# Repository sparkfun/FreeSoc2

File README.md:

SparkFun FreeSoc2
========================================

[*SparkFun FreeSoC2 (DEV-13714)*](https://www.sparkfun.com/products/13714)

The [FreeSoc2 is SparkFun's PSoC5LP development board](https://www.sparkfun.com/products/13714). It features a full onboard debugger, support for 5V and 3.3V IO voltages, and a CY8C5888AXI-LP096 processor with 256kB of flash, 64kB of SRAM and 2kB of EEPROM. The onboard oscillator can drive the processor at up to 80MHz, and the Cortex-M3 core provides superior performance.

The real power of the PSoC5LP isn't in the processor, however. Wrapped around the processor is a rich analog and digital programmable fabric which can be configured to provide many functions which would otherwise need to be realized in code (lowering system performance) or external circuitry (adding cost and board size). In addition, the highly flexible fabric means that most any function can be routed to most any pin, which makes this a wonderful tool for development and allows board layout errors to be solved, at least temporarily, pretty easily.

Repository Contents
-------------------

* **/Hardware** - Eagle design files (.brd, .sch)
* **/Production** - Production panel files (.brd)

Documentation
--------------
* **[Arduino Board Support](https://github.com/sparkfun/PSoC_Arduino_Support)** - Support board files for adding the FreeSoC2 to the Arduino IDE.
* **[Hookup Guide](https://learn.sparkfun.com/tutorials/freesoc2-hookup-guide-v14)** - Basic hookup guide for the FreeSoC2.

Product Versions
----------------
* [DEV-13714](https://www.sparkfun.com/products/13714) - V14
* _[DEV-13229 (RETIRED)](https://www.sparkfun.com/products/13229)- Initial Release_

Version History
---------------
* [v14](https://github.com/sparkfun/FreeSoc2/releases/tag/v14) -  V14 update
* [v01](https://github.com/sparkfun/FreeSoc2/releases/tag/v01) - Initial Release

License Information
-------------------
This product is _**open source**_! 

The **hardware** is released under [Creative Commons ShareAlike 4.0 International](https://creativecommons.org/licenses/by-sa/4.0/).

The **code** is beerware; if you see me (or any other SparkFun employee) at the local, and you've found our code helpful, please buy us a round!

Please use, reuse, and modify these files as you see fit. Please maintain attribution to SparkFun Electronics and release anything derivative under the same license.

Distributed as-is; no warranty is given.

- Your friends at SparkFun.

Collaborators
-------------

Thanks to Jon Moeller, for creating the first FreeSoC board and providing terrific feedback during the development of the FreeSoC2.
Thanks to Cypress Semiconductor, for providing feedback and working with us closely to ensure that the FreeSoC2 was the right product for the time.

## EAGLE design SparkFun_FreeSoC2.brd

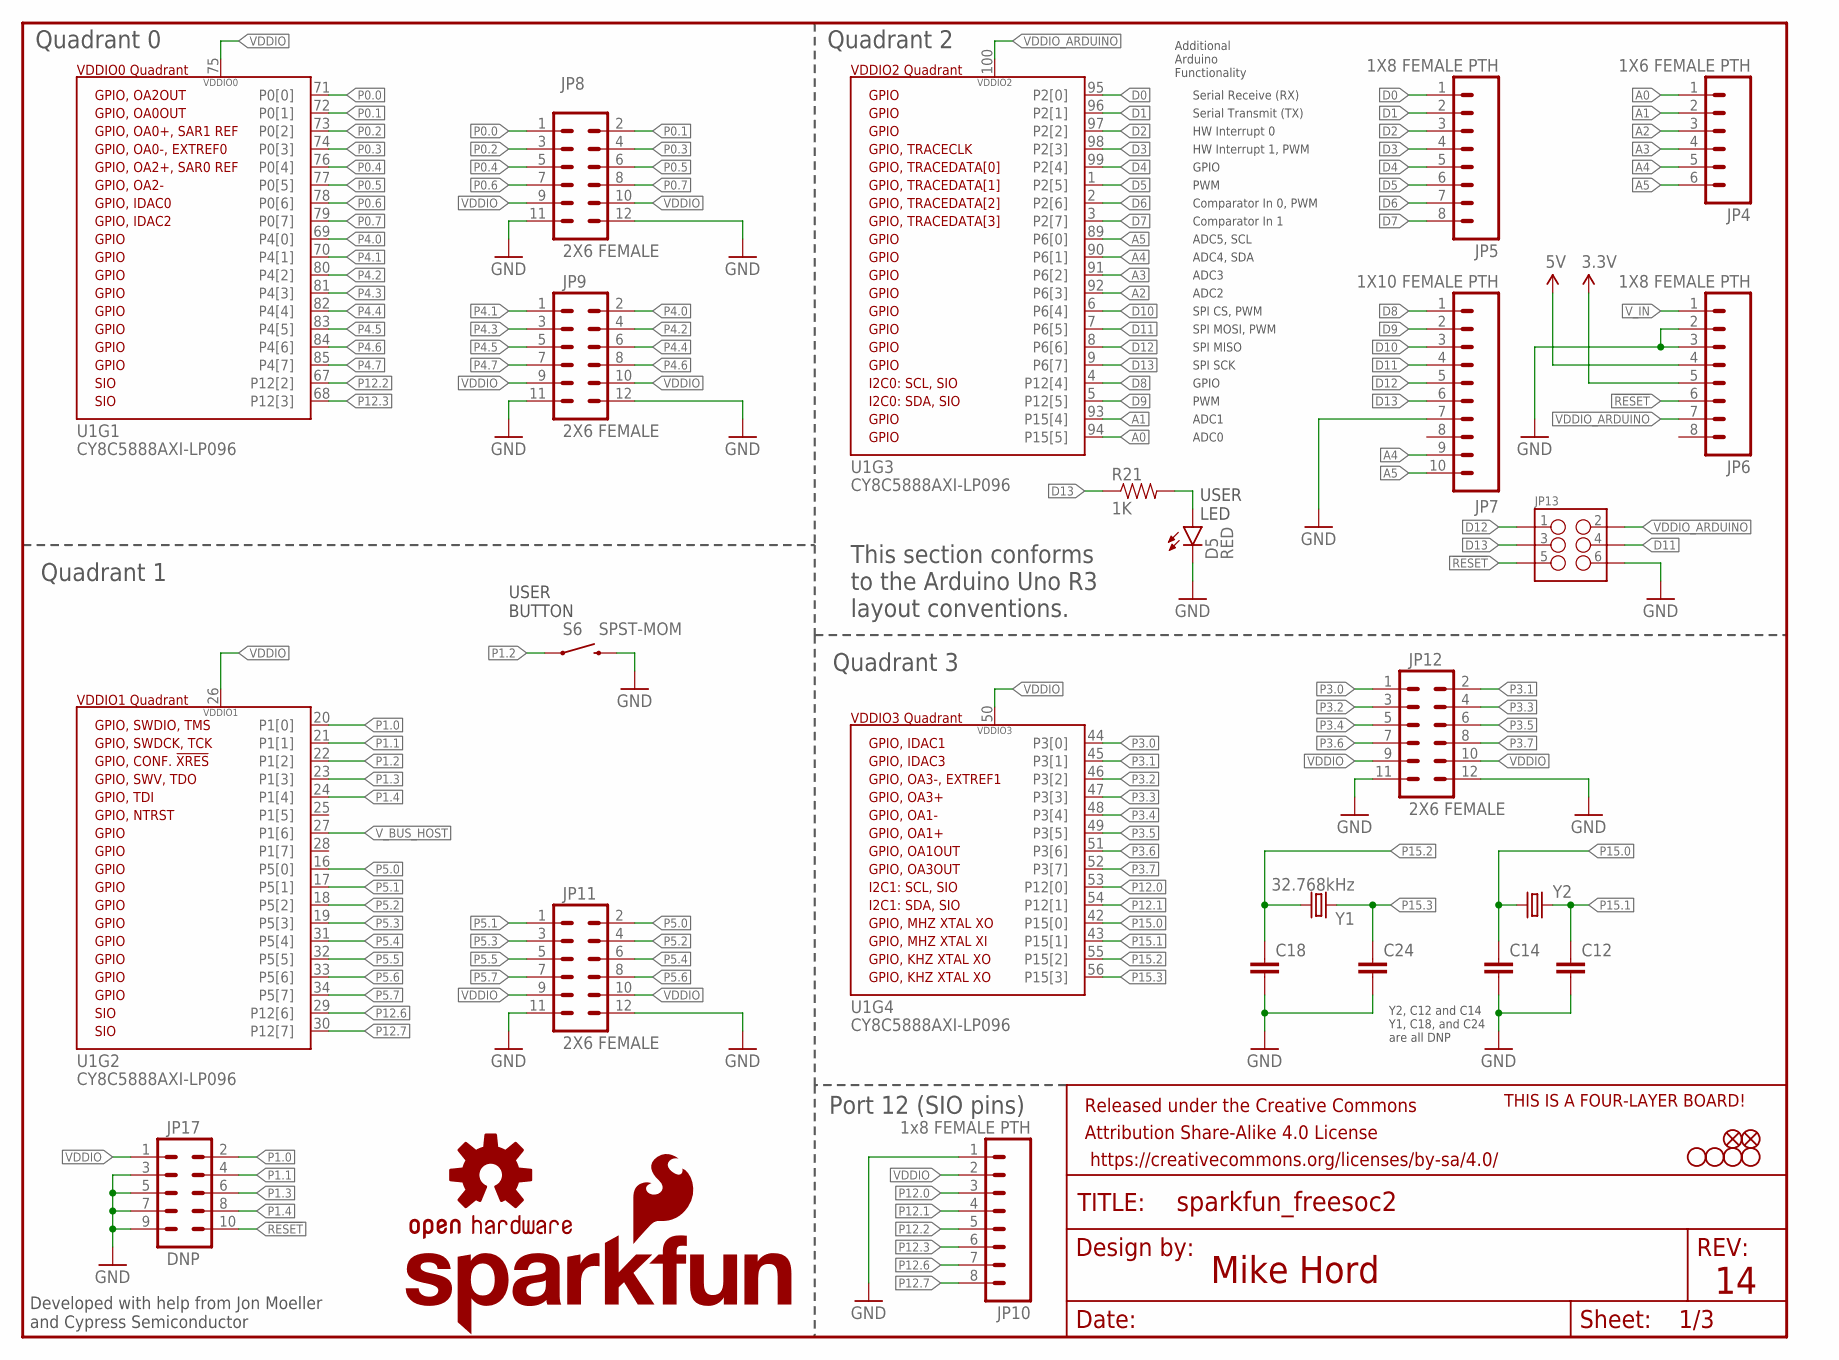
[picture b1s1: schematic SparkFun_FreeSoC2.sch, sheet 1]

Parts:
C12, C14, C18, C24: CAPPTH; CAP-PTH-SMALL
D5: RED; LED-0603
FID1, FID2: FIDUCIAL1X2; FIDUCIAL-1X2
FRAME3: FRAME-LETTERNO_PACKAGE; DUMMY
JP4: 1X6 FEMALE PTH; 1X06-SIP_LOCK
JP5, JP6: 1X8 FEMALE PTH; 1X08_LOCK
JP7: 1X10 FEMALE PTH; 1X10_LOCK
JP8, JP9, JP11, JP12: 2X6 FEMALE; 2X6
JP10: 1x8 FEMALE PTH; 1X08_LOCK
JP13: M03X22X3_SILK_MALE_PTH; 2X3
JP17: DNP; 2X5_PTH_SILK_.05
LOGO1: SFE_LOGO_NAME_FLAME.2_INCH; SFE_LOGO_NAME_FLAME_.2
LOGO2: OSHW-LOGOS; OSHW-LOGO-S
R21: 1K; 0603-RES@1
S6: SPST-MOM; TACTILE-SWITCH-SMD
STANDOFF1, STANDOFF2, STANDOFF3, STANDOFF4: STAND-OFF
U1: CY8C5888AXI-LP096; TQFP-100-14X14MM
U$1: FOUR_LAYER_WARNING
Y1: 32.768kHz; TC26H
Y2: CRYSTALHC49US; HC49US

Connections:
3.3V: JP6.5; also elsewhere on the board
5V: JP6.4; also elsewhere on the board
!RESET: JP6.6, JP13.5, JP17.10; also elsewhere on the board
A0: JP4.1, U1.94 (P15[5])
A1: JP4.2, U1.93 (P15[4])
A2: JP4.3, U1.92 (P6[3])
A3: JP4.4, U1.91 (P6[2])
A4: JP4.5, JP7.9, U1.90 (P6[1]); also elsewhere on the board
A5: JP4.6, JP7.10, U1.89 (P6[0]); also elsewhere on the board
D0: JP5.1, U1.95 (P2[0]); also elsewhere on the board
D1: JP5.2, U1.96 (P2[1]); also elsewhere on the board
D2: JP5.3, U1.97 (P2[2])
D3: JP5.4, U1.98 (P2[3])
D4: JP5.5, U1.99 (P2[4])
D5: JP5.6, U1.1 (P2[5])
D6: JP5.7, U1.2 (P2[6])
D7: JP5.8, U1.3 (P2[7])
D8: JP7.1, U1.4 (P12[4])
D9: JP7.2, U1.5 (P12[5])
D10: JP7.3, U1.6 (P6[4])
D11: JP7.4, JP13.4, U1.7 (P6[5])
D12: JP7.5, JP13.1, U1.8 (P6[6])
D13: JP7.6, JP13.3, R21.1, U1.9 (P6[7])
GND: C12.2, C14.2, C18.2, C24.2, D5.C, JP6.2, JP6.3, JP7.7, JP8.11, JP8.12, JP9.11, JP9.12, JP10.1, JP11.11, JP11.12, JP12.11, JP12.12, JP13.6, JP17.3, JP17.5, JP17.7, JP17.9, S6.3 (2); also elsewhere on the board
unnamed: D5.A, R21.2
P0.0: JP8.1, U1.71 (P0[0])
P0.1: JP8.2, U1.72 (P0[1])
P0.2: JP8.3, U1.73 (P0[2]); also elsewhere on the board
P0.3: JP8.4, U1.74 (P0[3]); also elsewhere on the board
P0.4: JP8.5, U1.76 (P0[4]); also elsewhere on the board
P0.5: JP8.6, U1.77 (P0[5])
P0.6: JP8.7, U1.78 (P0[6])
P0.7: JP8.8, U1.79 (P0[7])
P1.0: JP17.2, U1.20 (P1[0]); also elsewhere on the board
P1.1: JP17.4, U1.21 (P1[1]); also elsewhere on the board
P1.2: S6.1, U1.22 (P1[2])
P1.3: JP17.6, U1.23 (P1[3])
P1.4: JP17.8, U1.24 (P1[4])
P3.0: JP12.1, U1.44 (P3[0])
P3.1: JP12.2, U1.45 (P3[1])
P3.2: JP12.3, U1.46 (P3[2])
P3.3: JP12.4, U1.47 (P3[3])
P3.4: JP12.5, U1.48 (P3[4])
P3.5: JP12.6, U1.49 (P3[5])
P3.6: JP12.7, U1.51 (P3[6])
P3.7: JP12.8, U1.52 (P3[7])
P4.0: JP9.2, U1.69 (P4[0])
P4.1: JP9.1, U1.70 (P4[1])
P4.2: JP9.4, U1.80 (P4[2])
P4.3: JP9.3, U1.81 (P4[3])
P4.4: JP9.6, U1.82 (P4[4])
P4.5: JP9.5, U1.83 (P4[5])
P4.6: JP9.8, U1.84 (P4[6])
P4.7: JP9.7, U1.85 (P4[7])
P5.0: JP11.2, U1.16 (P5[0])
P5.1: JP11.1, U1.17 (P5[1])
P5.2: JP11.4, U1.18 (P5[2])
P5.3: JP11.3, U1.19 (P5[3])
P5.4: JP11.6, U1.31 (P5[4])
P5.5: JP11.5, U1.32 (P5[5])
P5.6: JP11.8, U1.33 (P5[6])
P5.7: JP11.7, U1.34 (P5[7])
P12.0: JP10.3, U1.53 (P12[0])
P12.1: JP10.4, U1.54 (P12[1])
P12.2: JP10.5, U1.67 (P12[2])
P12.3: JP10.6, U1.68 (P12[3])
P12.6: JP10.7, U1.29 (P12[6])
P12.7: JP10.8, U1.30 (P12[7])
P15.0: C14.1, U1.42 (P15[0]), Y2.1
P15.1: C12.1, U1.43 (P15[1]), Y2.2
P15.2: C18.1, U1.55 (P15[2]), Y1.2
P15.3: C24.1, U1.56 (P15[3]), Y1.1
VDDIO: JP8.9, JP8.10, JP9.9, JP9.10, JP10.2, JP11.9, JP11.10, JP12.9, JP12.10, JP17.1, U1.26 (VDDIO1), U1.50 (VDDIO3), U1.75 (VDDIO0); also elsewhere on the board
VDDIO_ARDUINO: JP6.7, JP13.2, U1.100 (VDDIO2); also elsewhere on the board
V_BUS_HOST: U1.27 (P1[6]); also elsewhere on the board
V_IN: JP6.1; also elsewhere on the board

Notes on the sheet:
Additional Arduino Functionality
Serial Receive (RX)
Serial Transmit (TX)
HW Interrupt 0
HW Interrupt 1, PWM
PWM
Comparator In 0, PWM
Comparator In 1
SPI CS, PWM
SPI MOSI, PWM
SPI MISO
SPI SCK
ADC0
ADC1
ADC5, SCL
ADC4, SDA
ADC2
ADC3
This section conforms to the Arduino Uno R3 layout conventions.
GPIO
Y2, C12 and C14 Y1, C18, and C24 are all DNP
Quadrant 1
Quadrant 2
Quadrant 0
Quadrant 3
Port 12 (SIO pins)
Developed with help from Jon Moeller and Cypress Semiconductor
USER BUTTON
USER LED
Mike Hord

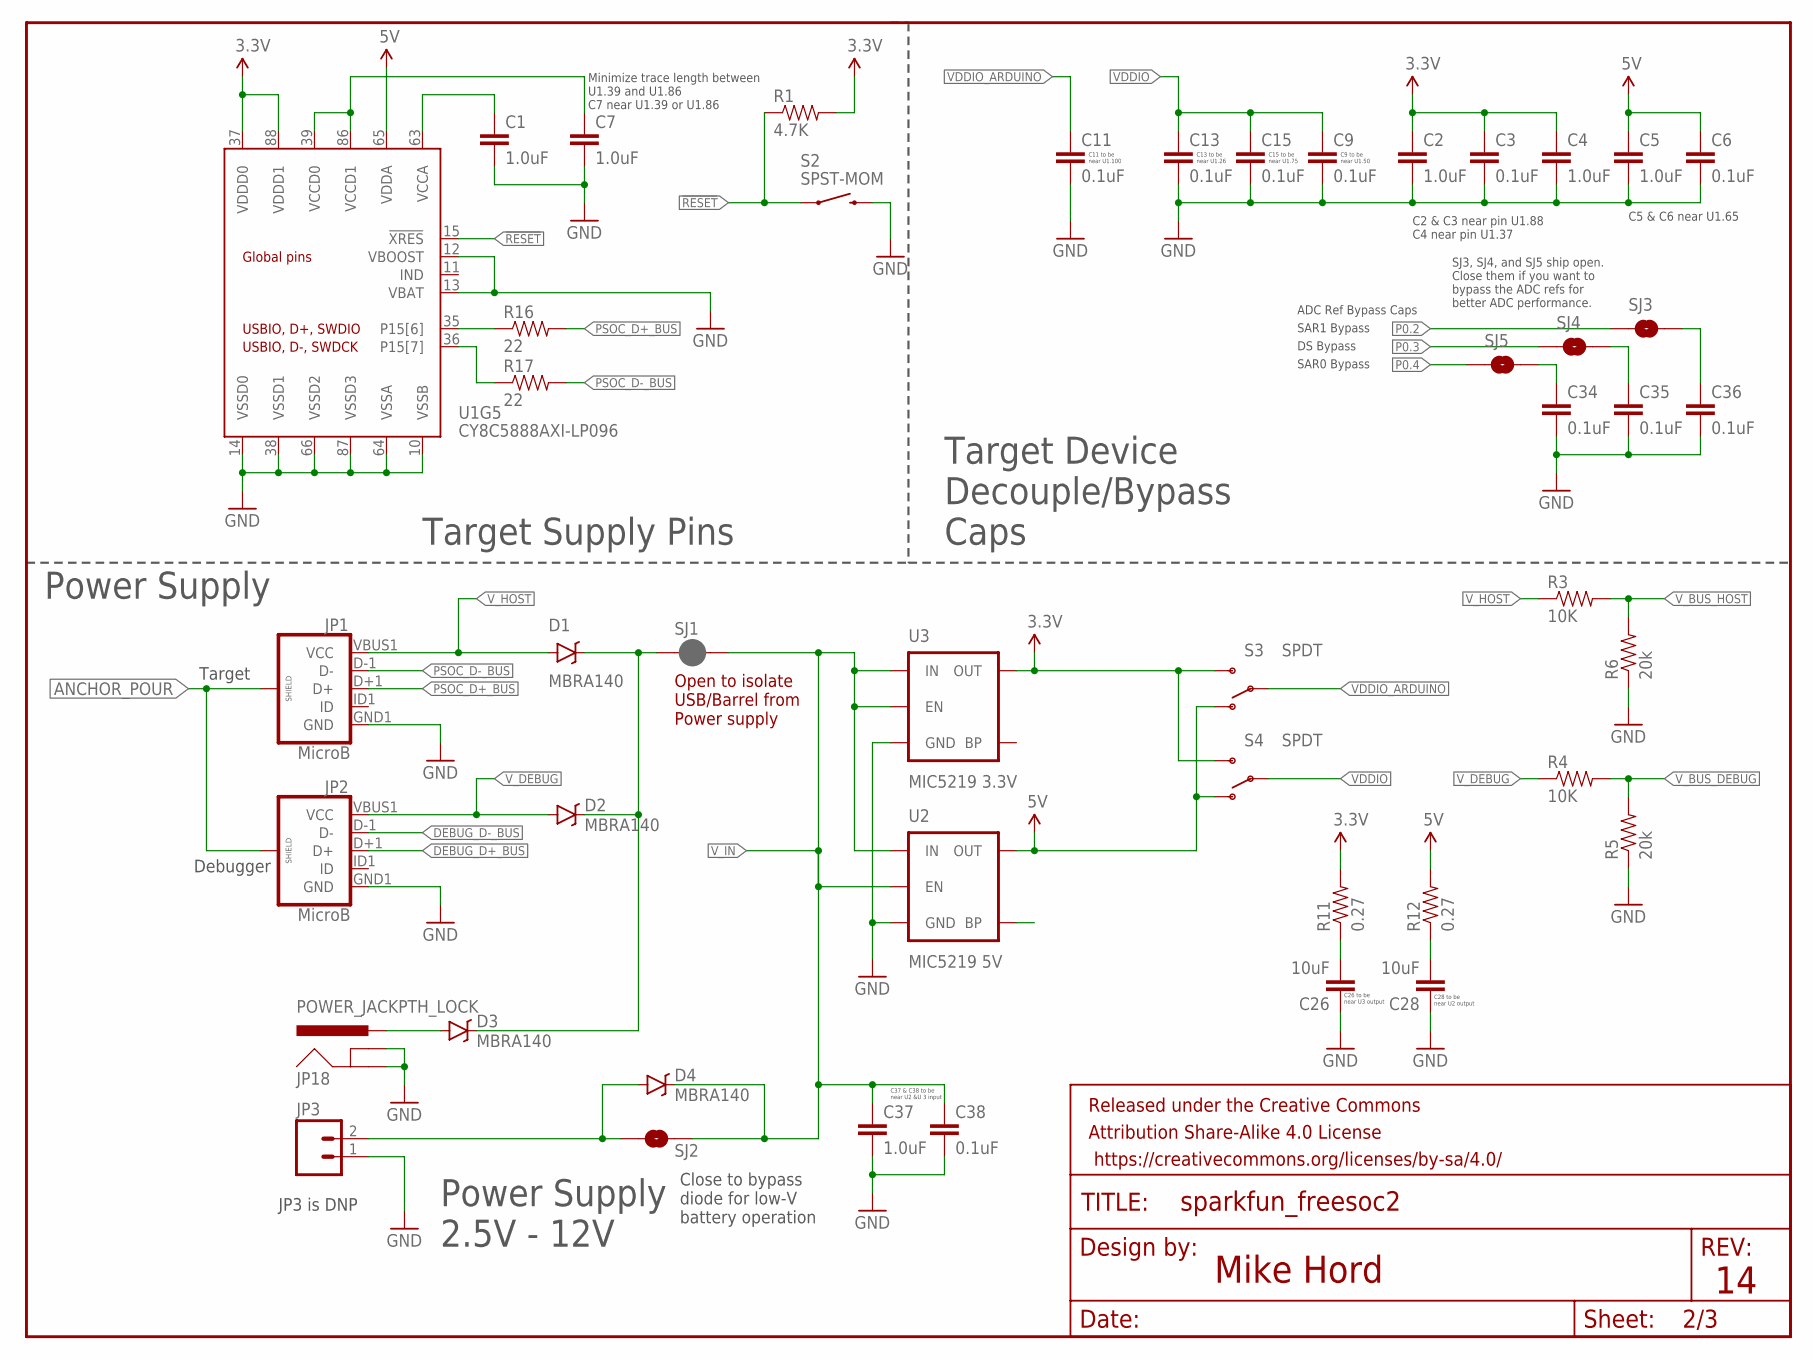
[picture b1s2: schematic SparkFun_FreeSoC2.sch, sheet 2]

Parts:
C1, C2, C4, C5, C7: 1.0uF; 0402-CAP
C3, C6, C9, C11, C13, C15, C34, C35, C36: 0.1uF; 0402-CAP
C26, C28: 10uF; 0805-CAP
C37: 1.0uF; 0603-CAP
C38: 0.1uF; 0603-CAP
D1, D2, D3, D4: MBRA140; SMA-DIODE
FRAME2: FRAME-LETTERNO_PACKAGE; DUMMY
JP1, JP2: MicroB; USB-B-MICRO-SMD_V03
JP3: M02JST-PTH-2; JST-2-PTH
JP18: POWER_JACKPTH_LOCK; POWER_JACK_PTH_LOCK
R1: 4.7K; 0603-RES
R3, R4: 10K; 0603-RES
R5, R6: 20k; 0603-RES
R11, R12: 0.27; 0603-RES
R16, R17: 22; 0402-RES
S2: SPST-MOM; TACTILE-SWITCH-SMD
S3, S4: SPDT; SWITCH-SPDT_LOCK.007S
SJ1: JUMPER-PAD-2-NC_BY_PASTE; PAD-JUMPER-2-NC_BY_PASTE_YES_SILK
SJ2: JUMPER-PAD-2-NOYES_SILK; PAD-JUMPER-2-NO_YES_SILK
SJ3, SJ4, SJ5: JUMPER-PAD-2-NO; PAD-JUMPER-2-NO_NO_SILK
U1: CY8C5888AXI-LP096; TQFP-100-14X14MM
U2: MIC5219 5V; SOT23-5
U3: MIC5219 3.3V; SOT23-5

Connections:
3.3V: C2.1, C3.1, C4.1, R1.2, R11.2, S3.3 (S), S4.3 (S), U1.37 (VDDD0), U1.88 (VDDD1), U3.5 (OUT); also elsewhere on the board
5V: C5.1, C6.1, R12.2, S3.1 (O), S4.1 (O), U1.65 (VDDA), U2.5 (OUT); also elsewhere on the board
!RESET: R1.1, S2.1, U1.15 (!XRES); also elsewhere on the board
ANCHOR_POUR: JP1.SHIELD1 (SHIELD), JP1.SHIELD2 (SHIELD), JP1.SHIELD3 (SHIELD), JP2.SHIELD1 (SHIELD), JP2.SHIELD2 (SHIELD), JP2.SHIELD3 (SHIELD)
DEBUG_D+_BUS: JP2.D+1 (D+); also elsewhere on the board
DEBUG_D-_BUS: JP2.D-1 (D-); also elsewhere on the board
GND: C1.2, C2.2, C3.2, C4.2, C5.2, C6.2, C7.2, C9.2, C11.2, C13.2, C15.2, C26.1, C28.1, C34.2, C35.2, C36.2, C37.2, C38.2, JP1.GND1 (GND), JP2.GND1 (GND), JP3.1, JP18.GND, JP18.GNDBREAK, R5.1, R6.1, S2.3 (2), U1.10 (VSSB), U1.12 (VBOOST), U1.13 (VBAT), U1.14 (VSSD0), U1.38 (VSSD1), U1.64 (VSSA), U1.66 (VSSD2), U1.87 (VSSD3), U2.2 (GND), U3.2 (GND); also elsewhere on the board
unnamed: C26.2, R11.1
unnamed: C34.1, SJ5.2
unnamed: C35.1, SJ4.2
unnamed: C36.1, SJ3.2
unnamed: C28.2, R12.1
unnamed: D3.A, JP18.PWR
unnamed: D1.C, D2.C, D3.C, SJ1.1
unnamed: D4.A, JP3.2, SJ2.1
P0.2: SJ3.1; also elsewhere on the board
P0.3: SJ4.1; also elsewhere on the board
P0.4: SJ5.1; also elsewhere on the board
PSOC_D+_BUS: JP1.D+1 (D+), R16.2
PSOC_D+_PAD: R16.1, U1.35 (P15[6])
PSOC_D-_BUS: JP1.D-1 (D-), R17.2
PSOC_D-_PAD: R17.1, U1.36 (P15[7])
VCCA: C1.1, U1.63 (VCCA)
VCCD: C7.1, U1.39 (VCCD0), U1.86 (VCCD1)
VDDIO: C9.1, C13.1, C15.1, S4.2; also elsewhere on the board
VDDIO_ARDUINO: C11.1, S3.2; also elsewhere on the board
V_BUS_DEBUG: R4.2, R5.2; also elsewhere on the board
V_BUS_HOST: R3.2, R6.2; also elsewhere on the board
V_DEBUG: D2.A, JP2.VBUS1 (VCC), R4.1
V_HOST: D1.A, JP1.VBUS1 (VCC), R3.1
V_IN: C37.1, C38.1, D4.C, SJ1.2, SJ2.2, U2.1 (IN), U2.3 (EN), U3.1 (IN), U3.3 (EN); also elsewhere on the board

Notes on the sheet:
Debugger
Target
C2 & C3 near pin U1.88 C4 near pin U1.37
C5 & C6 near U1.65
Minimize trace length between U1.39 and U1.86 C7 near U1.39 or U1.86
C9 to be near U1.50
C11 to be near U1.100
C13 to be near U1.26
C15 to be near U1.75
C26 to be near U3 output
C28 to be near U2 output
SAR1 Bypass
DS Bypass
SAR0 Bypass
ADC Ref Bypass Caps
SJ3, SJ4, and SJ5 ship open. Close them if you want to bypass the ADC refs for better ADC performance.
Power Supply
Target Device Decouple/Bypass Caps
Target Supply Pins
Power Supply 2.5V - 12V
Open to isolate USB/Barrel from Power supply
Close to bypass diode for low-V battery operation
JP3 is DNP
Mike Hord
C37 & C38 to be near U2 &U 3 input

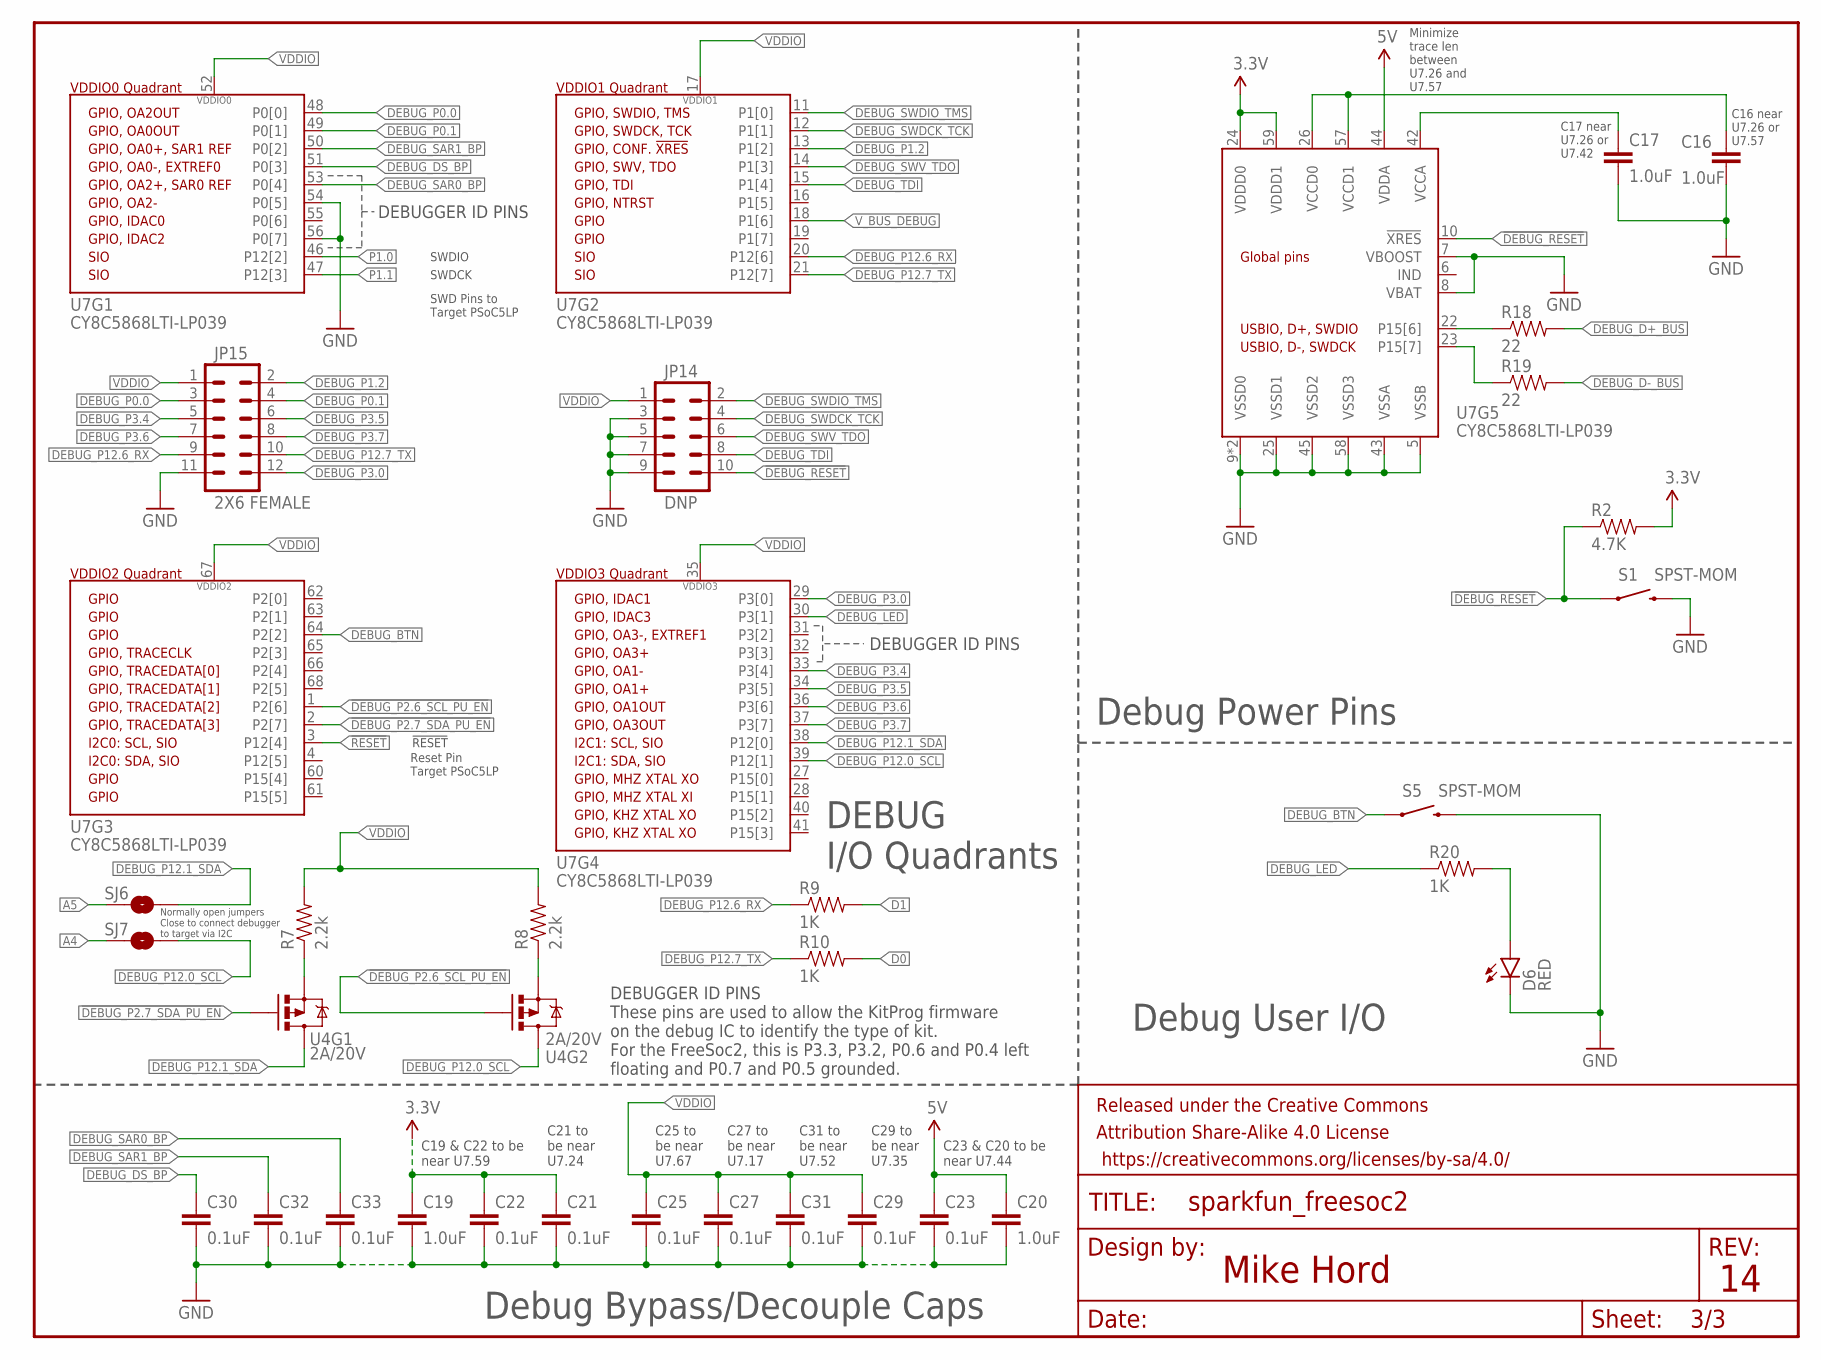
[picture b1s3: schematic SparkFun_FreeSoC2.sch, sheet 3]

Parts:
C16, C17, C19, C20: 1.0uF; 0402-CAP
C21, C22, C23, C25, C27, C29, C30, C31, C32, C33: 0.1uF; 0402-CAP
D6: RED; LED-0603
FRAME1: FRAME-LETTERNO_PACKAGE; DUMMY
JP14: DNP; 2X5_PTH_SILK_.05
JP15: 2X6 FEMALE; 2X6
R2: 4.7K; 0603-RES
R7, R8: 2.2k; 0603-RES
R9, R10, R20: 1K; 0603-RES@1
R18, R19: 22; 0402-RES
S1, S5: SPST-MOM; TACTILE-SWITCH-SMD
SJ6, SJ7: JUMPER-PAD-2-NO; PAD-JUMPER-2-NO_NO_SILK
U4: 2A/20V; SOT26
U7: CY8C5868LTI-LP039; QFN-68

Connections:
3.3V: C19.1, C21.1, C22.1, R2.2, U7.24 (VDDD0), U7.59 (VDDD1); also elsewhere on the board
5V: C20.1, C23.1, U7.44 (VDDA); also elsewhere on the board
!DEBUG_P2.6_SCL_PU_EN: U4.G2 (G), U7.1 (P2[6])
!DEBUG_P2.7_SDA_PU_EN: U4.G1 (G), U7.2 (P2[7])
!DEBUG_RESET: JP14.10, R2.1, S1.1, U7.10 (!XRES)
!RESET: U7.3 (P12[4]); also elsewhere on the board
A4: SJ7.1; also elsewhere on the board
A5: SJ6.1; also elsewhere on the board
D0: R10.2; also elsewhere on the board
D1: R9.2; also elsewhere on the board
DEBUG_BTN: S5.1, U7.64 (P2[2])
DEBUG_D+_BUS: R18.2; also elsewhere on the board
DEBUG_D+_PAD: R18.1, U7.22 (P15[6])
DEBUG_D-_BUS: R19.2; also elsewhere on the board
DEBUG_D-_PAD: R19.1, U7.23 (P15[7])
DEBUG_DS_BP: C30.1, U7.51 (P0[3])
DEBUG_LED: R20.1, U7.30 (P3[1])
DEBUG_P0.0: JP15.3, U7.48 (P0[0])
DEBUG_P0.1: JP15.4, U7.49 (P0[1])
DEBUG_P1.2: JP15.2, U7.13 (P1[2])
DEBUG_P3.0: JP15.12, U7.29 (P3[0])
DEBUG_P3.4: JP15.5, U7.33 (P3[4])
DEBUG_P3.5: JP15.6, U7.34 (P3[5])
DEBUG_P3.6: JP15.7, U7.36 (P3[6])
DEBUG_P3.7: JP15.8, U7.37 (P3[7])
DEBUG_P12.0_SCL: SJ7.2, U4.D2 (D), U7.39 (P12[1])
DEBUG_P12.1_SDA: SJ6.2, U4.D1 (D), U7.38 (P12[0])
DEBUG_P12.6_RX: JP15.9, R9.1, U7.20 (P12[6])
DEBUG_P12.7_TX: JP15.10, R10.1, U7.21 (P12[7])
DEBUG_SAR0_BP: C33.1, U7.53 (P0[4])
DEBUG_SAR1_BP: C32.1, U7.50 (P0[2])
DEBUG_SWDCK_TCK: JP14.4, U7.12 (P1[1])
DEBUG_SWDIO_TMS: JP14.2, U7.11 (P1[0])
DEBUG_SWV_TDO: JP14.6, U7.14 (P1[3])
DEBUG_TDI: JP14.8, U7.15 (P1[4])
GND: C16.2, C17.2, C19.2, C20.2, C21.2, C22.2, C23.2, C25.2, C27.2, C29.2, C30.2, C31.2, C32.2, C33.2, D6.C, JP14.3, JP14.5, JP14.7, JP14.9, JP15.11, S1.3 (2), S5.3 (2), U7.5 (VSSB), U7.7 (VBOOST), U7.8 (VBAT), U7.9 (VSSD0), U7.25 (VSSD1), U7.43 (VSSA), U7.45 (VSSD2), U7.54 (P0[5]), U7.56 (P0[7]), U7.58 (VSSD3), U7.69 (VSSD0); also elsewhere on the board
unnamed: R8.1, U4.S2 (S)
unnamed: R7.1, U4.S1 (S)
unnamed: C16.1, U7.26 (VCCD0), U7.57 (VCCD1)
unnamed: D6.A, R20.2
unnamed: C17.1, U7.42 (VCCA)
P1.0: U7.46 (P12[2]); also elsewhere on the board
P1.1: U7.47 (P12[3]); also elsewhere on the board
VDDIO: C25.1, C27.1, C29.1, C31.1, JP14.1, JP15.1, R7.2, R8.2, U7.17 (VDDIO1), U7.35 (VDDIO3), U7.52 (VDDIO0), U7.67 (VDDIO2); also elsewhere on the board
V_BUS_DEBUG: U7.18 (P1[6]); also elsewhere on the board

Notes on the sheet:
SWD Pins to Target PSoC5LP
SWDIO
SWDCK
!RESET
C19 & C22 to be near U7.59
C23 & C20 to be near U7.44
C21 to be near U7.24
C25 to be near U7.67
C27 to be near U7.17
C29 to be near U7.35
C31 to be near U7.52
C16 near U7.26 or U7.57
C17 near U7.26 or U7.42
Minimize trace len between U7.26 and U7.57
DEBUG I/O Quadrants
Debug Bypass/Decouple Caps
Debug User I/O
Debug Power Pins
DEBUGGER ID PINS
DEBUGGER ID PINS These pins are used to allow the KitProg firmware on the debug IC to identify the type of kit. For the FreeSoc2, this is P3.3, P3.2, P0.6 and P0.4 left floating and P0.7 and P0.5 grounded.
Reset Pin Target PSoC5LP
Normally open jumpers Close to connect debugger to target via I2C
Mike Hord

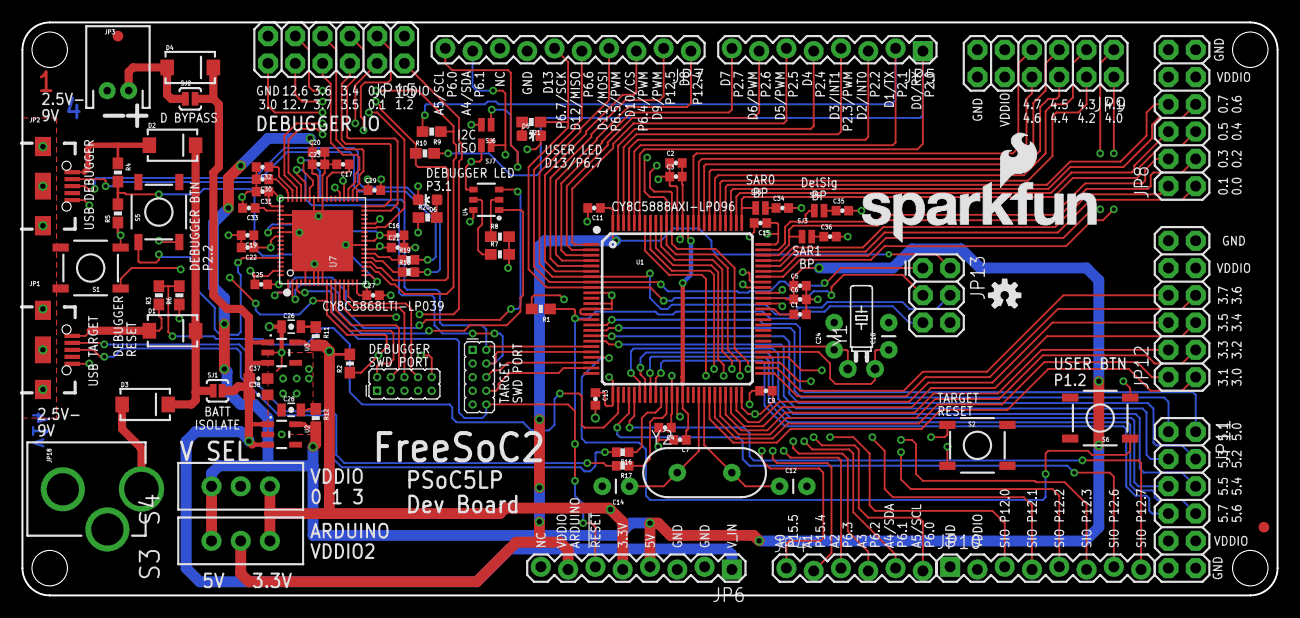
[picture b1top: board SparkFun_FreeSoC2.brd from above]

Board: 4 copper layers, 116.8 x 53.3 mm, 110 parts (0 on the bottom side), 127 nets.

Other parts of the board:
U$2: CREATIVE_COMMONS@1

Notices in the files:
parts and their libraries:
SparkFun-Aesthetics: Licensing: Creative Commons ShareAlike 4.0 International - https://creativecommons.org/licenses/by-sa/4.0
SparkFun-Aesthetics: Released under the Creative Commons Attribution Share-Alike 4.0 License
SparkFun-Aesthetics: Released under the Creative Commons
